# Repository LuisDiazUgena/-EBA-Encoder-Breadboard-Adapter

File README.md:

#EBA Encoder-Breadboard-Adapter

Are you mad of your encoder moving around your breadboard? This is for you! A single side Encoder breadboard adapter.

It have a hardware led to show when the pushbutton has been clicked.

##Pictures

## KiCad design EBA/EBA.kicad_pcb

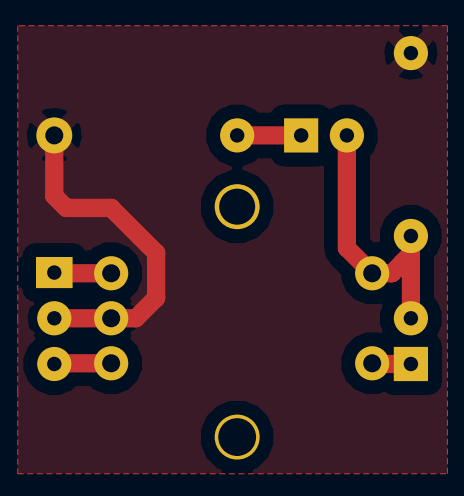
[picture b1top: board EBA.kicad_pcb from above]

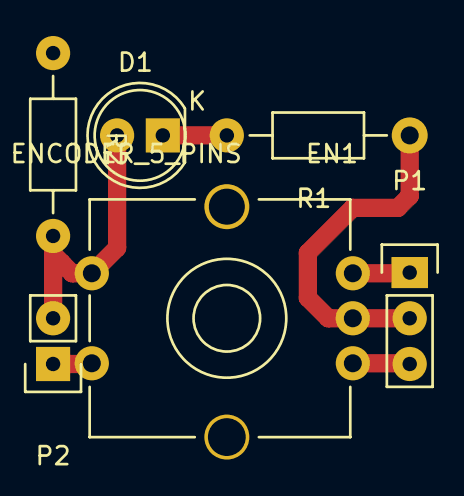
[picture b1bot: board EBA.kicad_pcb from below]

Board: 2 copper layers, 6 parts (6 on the bottom side), 6 nets.

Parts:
D1: LED; LED-5MM
EN1: ENCODER_5_PINS
P1: CONN_01X03; Pin_Header_Straight_1x03
P2: CONN_01X02; Pin_Header_Straight_1x02
R1, R2: R; Resistor_Horizontal_RM10mm

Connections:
GND: EN1.2, P1.2, R1.1, R2.1
unnamed: D1.1, R1.2
unnamed: D1.2, EN1.5, P2.2, R2.2
unnamed: EN1.1, P1.3
unnamed: EN1.3, P1.1
unnamed: EN1.4, P2.1

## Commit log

2015-08-19 Added pcb
2015-08-19 Changed drill size of encoder pins to make it fit better
2015-08-19 Added pics
2015-08-19 Added info and pics
